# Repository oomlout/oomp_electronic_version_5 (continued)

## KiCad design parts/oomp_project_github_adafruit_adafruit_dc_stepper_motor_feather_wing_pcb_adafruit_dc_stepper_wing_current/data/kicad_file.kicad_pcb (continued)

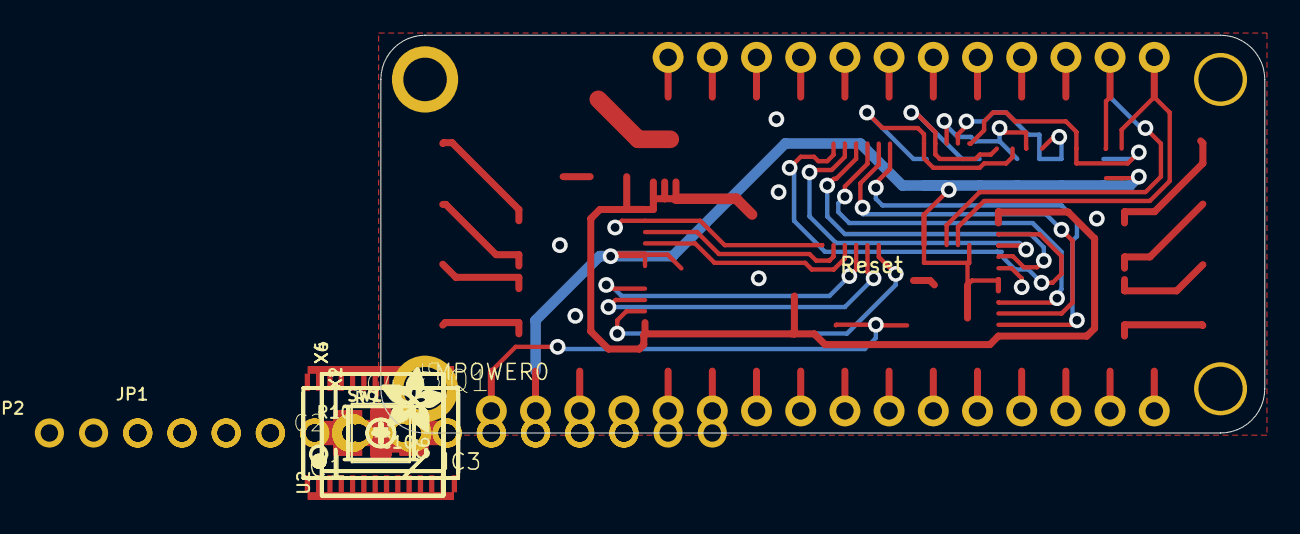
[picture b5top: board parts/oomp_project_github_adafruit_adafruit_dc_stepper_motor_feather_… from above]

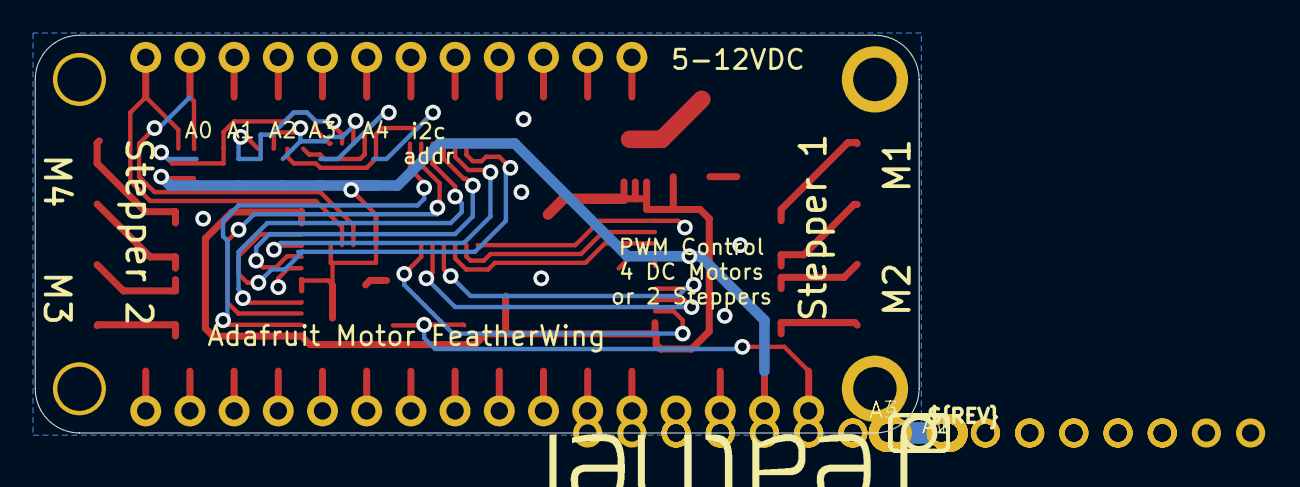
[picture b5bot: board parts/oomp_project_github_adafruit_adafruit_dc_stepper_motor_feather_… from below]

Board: 16 copper layers, 50.8 x 22.9 mm, 34 parts (7 on the bottom side), 56 nets.

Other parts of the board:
U$1: SYMBOL_PLUS
U$2: SYMBOL_MINUS
U$5: ADAFRUIT_3.5MM
U$6: FEATHERLOGO
U$8: PCBFEAT-REV-040

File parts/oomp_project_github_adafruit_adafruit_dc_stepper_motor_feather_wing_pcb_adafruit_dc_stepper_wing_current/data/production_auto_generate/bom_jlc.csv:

Comment,Designator,Footprint,LCSC Part #
,JP1,Adafruit DC+Stepper Wing-import-fps:1X12_ROUND,C7501588
,JP2,Adafruit DC+Stepper Wing-import-fps:1X16_ROUND,C7501270
,U$5,Adafruit DC+Stepper Wing-import-fps:ADAFRUIT_3.5MM,
,SW1,Adafruit DC+Stepper Wing-import-fps:BTN_KMR2_4.6X2.8,
,U$6,Adafruit DC+Stepper Wing-import-fps:FEATHERLOGO,
,U$8,Adafruit DC+Stepper Wing-import-fps:PCBFEAT-REV-040,
,"A0,A1,A2,A3,A4",Adafruit DC+Stepper Wing-import-fps:SOLDERJUMPER_REFLOW_NOPASTE,
,U$2,Adafruit DC+Stepper Wing-import-fps:SYMBOL_MINUS,
,U$1,Adafruit DC+Stepper Wing-import-fps:SYMBOL_PLUS,
,"X1,X2,X4,X6",Adafruit DC+Stepper Wing-import-fps:TERMBLOCK_1X2-3.5MM,
0.1uF,C2,Adafruit DC+Stepper Wing-import-fps:0805-NO,
10K,"R9,R10",Adafruit DC+Stepper Wing-import-fps:RESPACK_4X0603,C98220
10uF,"C6,C10",Adafruit DC+Stepper Wing-import-fps:0805-NO,
1K,R4,Adafruit DC+Stepper Wing-import-fps:0805-NO,C17513
1X2-3.5MM,MPOWER0,Adafruit DC+Stepper Wing-import-fps:1X2-3.5MM,C492401
47uF+/16v,C5,Adafruit DC+Stepper Wing-import-fps:PANASONIC_C,
47uF/16v,C4,Adafruit DC+Stepper Wing-import-fps:PANASONIC_C,
AON7401,Q1,Adafruit DC+Stepper Wing-import-fps:POWERDI3333,
FEATHERWING,MS1,Adafruit DC+Stepper Wing-import-fps:FEATHERWING,
"FIDUCIAL""""","U$3,U$4",Adafruit DC+Stepper Wing-import-fps:FIDUCIAL_1MM,
Green,LED1,Adafruit DC+Stepper Wing-import-fps:CHIPLED_0805_NOOUTLINE,
PCA9685,U2,Adafruit DC+Stepper Wing-import-fps:TSSOP28,
TB6612FNG,"IC1,IC3",Adafruit DC+Stepper Wing-import-fps:SSOP24,

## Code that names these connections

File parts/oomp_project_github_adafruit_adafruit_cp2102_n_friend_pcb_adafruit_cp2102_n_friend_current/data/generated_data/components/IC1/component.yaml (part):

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        pin_number: '4'
        pin_name: '4'
    - number: '11'
      name: GPIO3
      electrical_type: bidirectional
      graphic_style: line
      local_position:
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      position:
        x: 149.86
        y: 93.98
      net: GPIO3
      net_aliases:
      - GPIO3
      net_scope: global
      no_connect: false
      connected_to:
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        pin_number: '5'
        pin_name: '5'
    - number: '12'
      name: GPIO2
      electrical_type: bidirectional
      graphic_style: line
      local_position:
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      position:
        x: 149.86
        y: 91.44
      net: GPIO2
      net_aliases:
      - GPIO2
      net_scope: global
      no_connect: false
      connected_to:
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        pin_number: '6'
        pin_name: '6'
    - number: '13'
      name: GPIO1/RXLED
      electrical_type: bidirectional
      graphic_style: line
      local_position:
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        pin_number: C
        pin_name: C
    - number: '14'
      name: GPIO0/TXLED
      electrical_type: bidirectional
      graphic_style: line
      local_position:
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    - F.Cu
    - F.Mask
    - F.Paste
    net: GPIO3
    net_number: null
    pin_function: null
    pin_type: null
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    - F.Cu
    - F.Mask
    - F.Paste
    net: GPIO2
    net_number: null
    pin_function: null
    pin_type: null
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    status: no_named_net
  - pin_or_pad_number: '11'
    schematic_nets:
    - GPIO3
    pcb_nets:
    - GPIO3
    status: agree
  - pin_or_pad_number: '12'
    schematic_nets:
    - GPIO2
    pcb_nets:
    - GPIO2
    status: agree
  - pin_or_pad_number: '13'
    schematic_nets: []
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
